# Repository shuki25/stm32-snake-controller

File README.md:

# stm32-snake-controller
 A snake game controller board designed to use with WS2812B LED grid and SNES controller

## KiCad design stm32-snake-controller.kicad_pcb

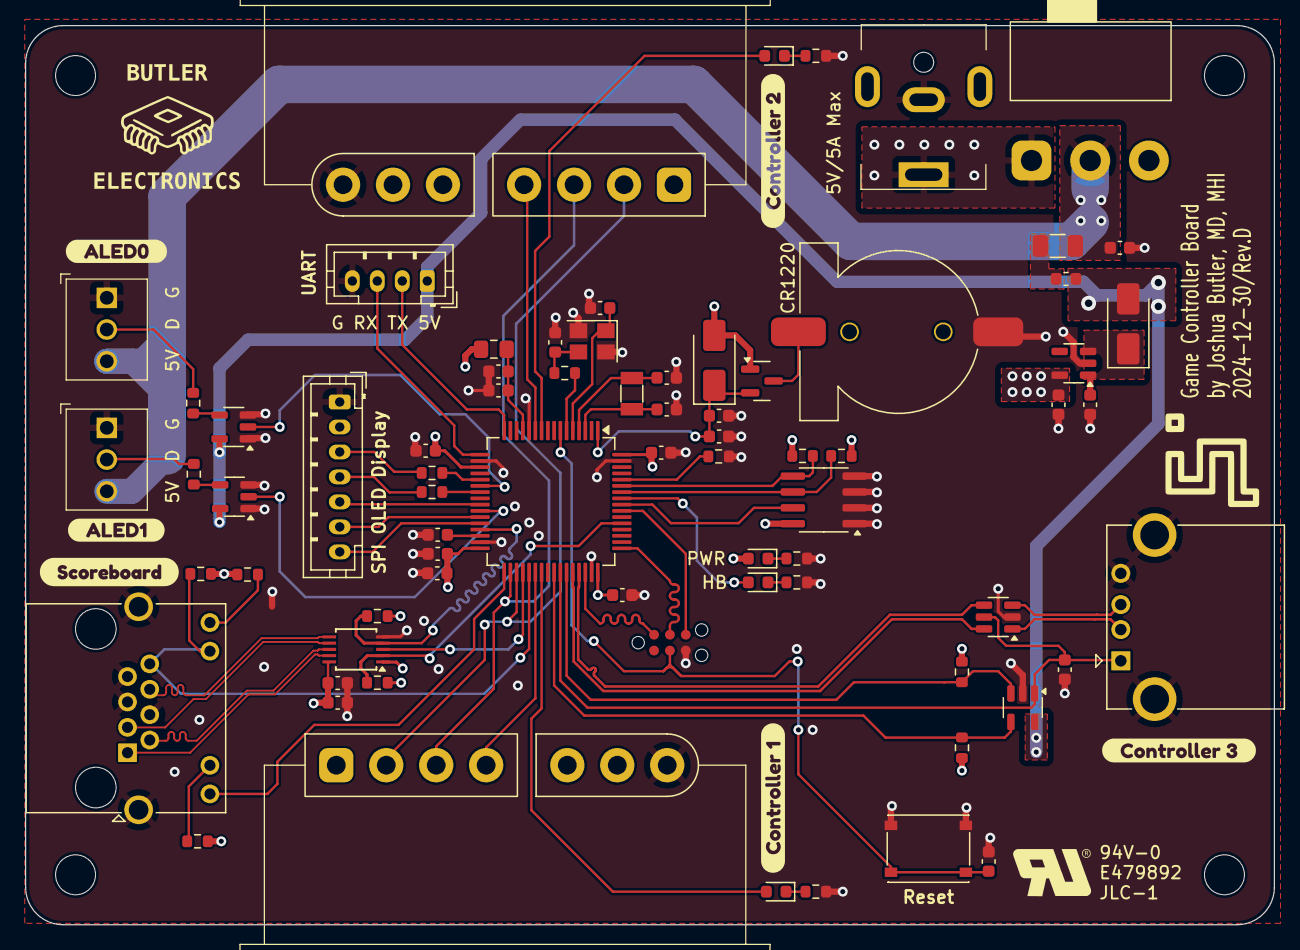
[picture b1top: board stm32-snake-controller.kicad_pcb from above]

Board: 4 copper layers, 100.0 x 72.0 mm, 83 parts (0 on the bottom side), 68 nets.

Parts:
BT101: Battery_Cell; BatteryHolder_CR1220
C101, C102: 15pF; C_0603_1608Metric
C103, C109, C110, C111, C112, C113, C116, C602: 100nF; C_0603_1608Metric
C104, C201: 22uF; C_0603_1608Metric
C105, C106: 10pF; C_0603_1608Metric
C107, C114, C202, C501: 4.7uF; C_0603_1608Metric
C108, C115, C601: 1uF; C_0603_1608Metric
D101, D106: SS34; D_SMA
D102: YELLOW; LED_0603_1608Metric
D103, D104: BLUE; LED_0603_1608Metric
D105: RED; LED_0603_1608Metric
F101: Polyfuse_Small; Fuse_1206_3216Metric
FB101: 600@100MHz; L_0805_2012Metric_Pad1.15x1.40mm_HandSolder
H101, H102, H103, H104: MountingHole; MountingHole_3.2mm_M3
J101: Barrel_Jack_MountingPin; DC_Power_Jack_PJ-063BH
J102: Tag Connector; TC2030-IDC-NL
J103: JST 2.54 Header; JST_PH_B4B-PH-K_1x04_P2.00mm_Vertical
J301, J302: Conn_01x03; molex-39773-0003
J401, J402: Conn_01x07; SNES_Controller_Port_Horizontal
J501: USB_A; USB_A_CONNFLY_DS1095-WNR0
J601: 8P8C_LED_Shielded; RJ45_Amphenol_RJHSE538X
L101: L_Ferrite_Small; L_0603_1608Metric
OLED101: OLED_SPI; JST_PH_B7B-PH-K_1x07_P2.00mm_Vertical
Q101: AO3501A; SOT-23
R101: 0; R_0603_1608Metric
R102, R103: 47; R_0603_1608Metric
R104, R108, R109, R111, R112, R602, R603: 1K5; R_0603_1608Metric
R105, R106, R107: 2K2; R_0603_1608Metric
R110, R501, R502, R601: 10K; R_0603_1608Metric
R301, R302: 100; R_0603_1608Metric
SW101: SW_SPDT; Slide_Switch_SPDT_SS-12D06L5
SW102: SW_Push; XKB-Connectivity-TS-1187A-B-A-B
U101: USBLC6-2SC6; SOT-23-6
U102: M24C64-RMN; SOIC-8_3.9x4.9mm_P1.27mm
U103: STM32F446RCTx; LQFP-64_10x10mm_P0.5mm
U201: XC6220B331MR-G; SOT-23-5
U301, U302: 74AHCT1G125; SOT-23-5
U501: STMPS2141STR; SOT-23-5
U601: PCA9615DP; TSSOP-10_3x3mm_P0.5mm
Y101: 32.768kHz; Crystal_SMD_3215-2Pin_3.2x1.5mm
Y102: 16MHz; Crystal_SMD_3225-4Pin_3.2x2.5mm
kibuzzard-65A37CF1: G***; kibuzzard-65A37CF1
kibuzzard-65A37D11: G***; kibuzzard-65A37D11
kibuzzard-65A37DD1: G***; kibuzzard-65A37DD1
kibuzzard-65A37F1A: G***; kibuzzard-65A37F1A
kibuzzard-65A37F11: G***; kibuzzard-65A37F11
kibuzzard-65E6C2BD: G***; kibuzzard-65E6C2BD

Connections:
+3.3VA: C108.1, C110.1, FB101.1, U103.13 (VREF+)
+3V3: C107.1, C109.1, C111.1, C112.1, C113.1, C202.1, C601.1, C602.1, D105.2 (A), D106.2 (A), FB101.2, J401.1, J402.1, OLED101.2 (VCC), Q101.1 (G), R104.2, R109.2, R111.2, R112.2, R501.2, R502.2, R601.2, R602.1, R603.1, U102.8 (VCC), U103.19 (VDD), U103.32 (VDD), U103.48 (VDD), U103.64 (VDD), U201.5 (VOUT), U601.1 (V_{DD(A)}), U601.10 (V_{DD(B)})
+5V: D101.2 (A), J103.1, L101.2, U301.5 (VCC), U302.5 (VCC), U501.5 (IN)
/BAT+: BT101.1 (+), Q101.3 (D)
/D_N: U101.6 (I/O1), U103.44 (PA11)
/D_P: U101.4 (I/O2), U103.45 (PA12)
/HSE_IN: C105.1, U103.5 (PH0), Y102.1
/HSE_OUT: R101.1, U103.6 (PH1)
/I2C_LED: J601.9, U103.33 (PB12)
/LDO_3V3/5V: C201.2, D101.1 (K), U201.1 (VIN), U201.3 (CE)
/LED_GRID0: U103.22 (PA6), U301.2
/LED_GRID1: U103.26 (PB0), U302.2
/LED_HB: D102.2 (A), U103.57 (PB5)
/LED_SNES0: D104.2 (A), U103.39 (PC8)
/LED_SNES1: D103.2 (A), U103.10 (PC2)
/LSE_IN: C101.2, U103.3 (PC14), Y101.2
/LSE_OUT: C102.2, U103.4 (PC15), Y101.1
/MOSI: R102.2, U103.23 (PA7)
/NRST: C103.1, J102.3, SW102.1, U103.7 (NRST)
/OLED_CE: OLED101.6 (CS), U103.27 (PB1)
/OLED_DC: OLED101.7 (DC), U103.28 (PB2)
/OLED_RST: OLED101.5 (RESET), U103.25 (PC5)
/SB_EN: U103.36 (PB15), U601.3 (EN)
/SB_LINK: J601.8, J601.11, R601.1, U103.37 (PC6)
/SB_SCL: R112.1, U103.29 (PB10), U601.4 (SCL)
/SB_SDA: R111.1, U103.53 (PC12), U601.2 (SDA)
/SCL: R109.1, U102.6 (SCL), U103.58 (PB6)
/SDA: R104.1, U102.5 (SDA), U103.59 (PB7)
/SNES_CLK: J401.2, J402.2, U103.35 (PB14)
/SNES_DATA0: J401.4, U103.38 (PC7)
/SNES_DATA1: J402.4, U103.11 (PC3)
/SNES_LATCH: J401.3, J402.3, U103.34 (PB13)
/SPI_CLK: R103.1, U103.21 (PA5)
/SWCLK: J102.4, U103.49 (PA14)
/SWDIO: J102.2, U103.46 (PA13)
/SWO: J102.6, U103.55 (PB3)
/UART_RX: J103.3, U103.17 (PA3)
/UART_TX: J103.2, U103.16 (PA2)
/USB_D_N: J501.2 (D-), U101.1 (I/O1)
/USB_D_P: J501.3 (D+), U101.3 (I/O2)
/USB_OTG_EN: R501.1, U103.41 (PA8), U501.4 (EN)
/USB_OTG_OC: R502.1, U103.43 (PA10), U501.3 (~FAULT)
/USB_OTG_VSEN: C501.1, J501.1 (VBUS), U101.5 (VBUS), U103.42 (PA9), U501.1 (OUT)
/VBAT: C115.1, C116.1, D106.1 (K), Q101.2 (S), U103.1 (VBAT)
/scoreboard/SCL_N: J601.6, U601.6 (DSCLM)
/scoreboard/SCL_P: J601.3, U601.7 (DSCLP)
/scoreboard/SDA_N: J601.1, U601.9 (DSDAM)
/scoreboard/SDA_P: J601.2, U601.8 (DSDAP)
/~EEPROM: U102.7 (~WC), U103.56 (PB4)
GND: BT101.2 (-), C101.1, C102.1, C103.2, C104.1, C105.2, C106.2, C107.2, C108.2, C109.2, C110.2, C111.2, C112.2, C113.2, C114.2, C115.2, C116.2, C201.1, C202.2, C501.2, C601.2, C602.2, J101.2, J102.5, J103.4, J301.1, J302.1, J401.7, J402.7, J501.4 (GND), J501.5 (Shield), J601.4, J601.5, J601.7, J601.SH, OLED101.1 (GND), R105.2, R106.2, R107.2, R108.2, R110.1, SW102.2, U101.2 (GND), U102.1 (E0), U102.2 (E1), U102.3 (E2), U102.4 (VSS), U103.12 (VSSA), U103.18 (VSS), U103.31 (VSS), U103.47 (VSS), U103.63 (VSS), U201.2 (GND), U301.1, U301.3 (GND), U302.1, U302.3 (GND), U501.2 (GND), U601.5 (V_{SS}), Y102.2, Y102.4
unnamed: C106.1, R101.2, Y102.3
unnamed: D102.1 (K), R105.1
unnamed: D103.1 (K), R106.1
unnamed: D104.1 (K), R107.1
unnamed: D105.1 (K), R108.1
unnamed: F101.2, L101.1
unnamed: J301.2, R301.2
unnamed: J302.2, R302.2
unnamed: J601.10, R602.2
unnamed: J601.12, R603.2
unnamed: OLED101.4 (MOSI), R102.1
unnamed: OLED101.3 (SCLK), R103.2
unnamed: R301.1, U301.4
unnamed: R302.1, U302.4
unnamed: J101.1, SW101.1 (A)
unnamed: R110.2, U103.60 (BOOT0)
unnamed: C114.1, U103.30 (VCAP1)
VBUS: C104.2, F101.1, J301.3, J302.3, SW101.2 (B)

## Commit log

2023-12-25 add initial schematic design
2023-12-27 update schematic
2023-12-29 replace micro usb to barrel jack
2024-01-01 update SPI pins for OLED
2024-01-01 add SNES controller connector drawing
2024-01-01 update title block
2024-01-02 add power switch for USB Host
2024-01-14 change footprint
2024-01-15 add mounting holes and reassign pins
2024-01-15 renumerate annotations
2024-01-15 update PCB design
2024-01-15 add SNES connector image
2024-01-15 update BOM
2024-01-15 add production files
2024-01-15 adjust footprint placement
2024-01-15 update production files
2024-01-15 add origin point for drill files
2024-01-27 add step file
2024-01-27 update part number
2024-01-27 add dimension in user comment
2024-01-29 update schematic and pcb design to rev-b
2024-02-04 add power switch, rearrange pins for OLED display
2024-02-28 add ferrite bead, 2nd i2c line, change power
2024-03-05 add scoreboard connector
    - add ethernet jack for scoreboard connection
2024-03-12 remove pull-down resistor
    - The original schematic had pull-down resistors for link detection, after a breadboard testing, it failed. Looked at the oscilloscope, it showed that the signal voltage dropped, acting like a voltag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
2024-03-12 update pdf
2024-03-13 fix differential traces
2024-03-22 add pull-up resistor for 2nd I2C lines
2024-04-09 update settings
2024-04-09 add 3d model
2025-01-07 update silkscreen
